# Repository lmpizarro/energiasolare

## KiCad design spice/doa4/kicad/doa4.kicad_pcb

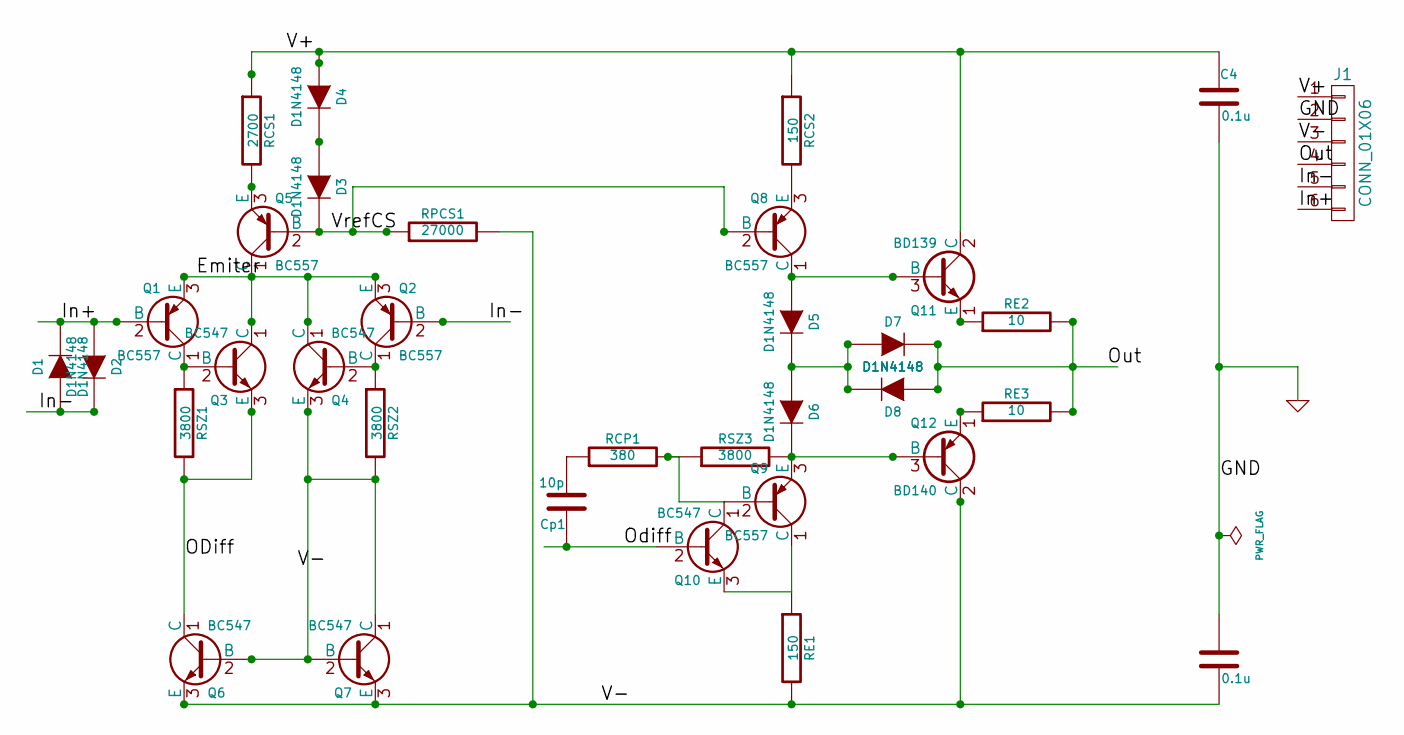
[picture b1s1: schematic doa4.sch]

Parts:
C4, C5: 0.1u; C_Rect_L4.6mm_W3.0mm_P2.50mm_MKS02_FKP02_Doa4
Cp1: 10p; C_Rect_L4.6mm_W3.0mm_P2.50mm_MKS02_FKP02_Doa4
D1: D1N4148; D_DO-41_SOD81_P2.54mm_Vertical_AnodeUp
D2, D3, D4, D5, D6, D7, D8: D1N4148; D_DO-41_SOD81_P2.54mm_Vertical_AnodeUp_Doa4
J1: CONN_01X06; j990
Q1, Q2, Q5, Q8, Q9: BC557; TO-92_Molded_Wide_BCXXX
Q3, Q4, Q6, Q7, Q10: BC547; TO-92_Molded_Wide_BCXXX
Q11: BD139; TO-126_Vertical_Doa4
Q12: BD140; TO-126_Vertical_Doa4
RCP1: 380; R_Axial_DIN0207_L6.3mm_D2.5mm_P2.54mm_Vertical_Doa4
RCS1: 2700; R_Axial_DIN0207_L6.3mm_D2.5mm_P2.54mm_Vertical_Doa4
RCS2: 150; R_Axial_DIN0207_L6.3mm_D2.5mm_P2.54mm_Vertical_Doa4
RE1: 150; R_Axial_DIN0207_L6.3mm_D2.5mm_P2.54mm_Vertical_Doa4
RE2, RE3: 10; R_Axial_DIN0207_L6.3mm_D2.5mm_P2.54mm_Vertical_Doa4
RPCS1: 27000; R_Axial_DIN0207_L6.3mm_D2.5mm_P2.54mm_Vertical_Doa4
RSZ1, RSZ2, RSZ3: 3800; R_Axial_DIN0207_L6.3mm_D2.5mm_P2.54mm_Vertical_Doa4

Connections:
/Emiter: Q1.3 (E), Q2.3 (E), Q3.1 (C), Q4.1 (C), Q5.1 (C)
/In+: D1.2 (K), D2.1 (A), J1.6, Q1.2 (B)
/In-: D1.1 (A), D2.2 (K), J1.5, Q2.2 (B)
/ODiff: Cp1.1, Q3.3 (E), Q6.1 (C), Q10.2 (B), RSZ1.2
/Out: D7.2 (K), D8.1 (A), J1.4, RE2.2, RE3.2
/V+: C4.1, D4.1 (A), J1.1, Q11.2 (C), RCS1.1, RCS2.1
/V-: C5.2, J1.3, Q6.3 (E), Q7.3 (E), Q12.2 (C), RE1.2, RPCS1.2
/VrefCS: D3.2 (K), Q5.2 (B), Q8.2 (B), RPCS1.1
GND: C4.2, C5.1, J1.2
unnamed: Cp1.2, RCP1.1
unnamed: D3.1 (A), D4.2 (K)
unnamed: D5.1 (A), Q8.1 (C), Q11.3 (B)
unnamed: D5.2 (K), D6.1 (A), D7.1 (A), D8.2 (K)
unnamed: D6.2 (K), Q9.3 (E), Q12.3 (B), RSZ3.2
unnamed: Q1.1 (C), Q3.2 (B), RSZ1.1
unnamed: Q2.1 (C), Q4.2 (B), RSZ2.1
unnamed: Q4.3 (E), Q6.2 (B), Q7.1 (C), Q7.2 (B), RSZ2.2
unnamed: Q5.3 (E), RCS1.2
unnamed: Q8.3 (E), RCS2.2
unnamed: Q9.2 (B), Q10.1 (C), RCP1.2, RSZ3.1
unnamed: Q9.1 (C), Q10.3 (E), RE1.1
unnamed: Q11.1 (E), RE2.1
unnamed: Q12.1 (E), RE3.1

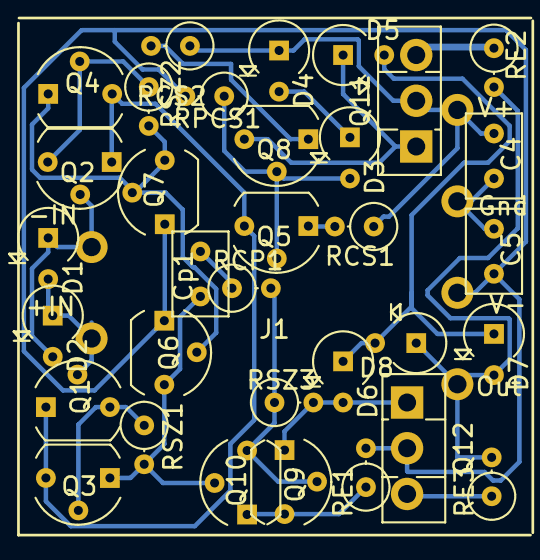
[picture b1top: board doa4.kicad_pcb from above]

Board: 2 copper layers, 34 parts (0 on the bottom side), 23 nets.

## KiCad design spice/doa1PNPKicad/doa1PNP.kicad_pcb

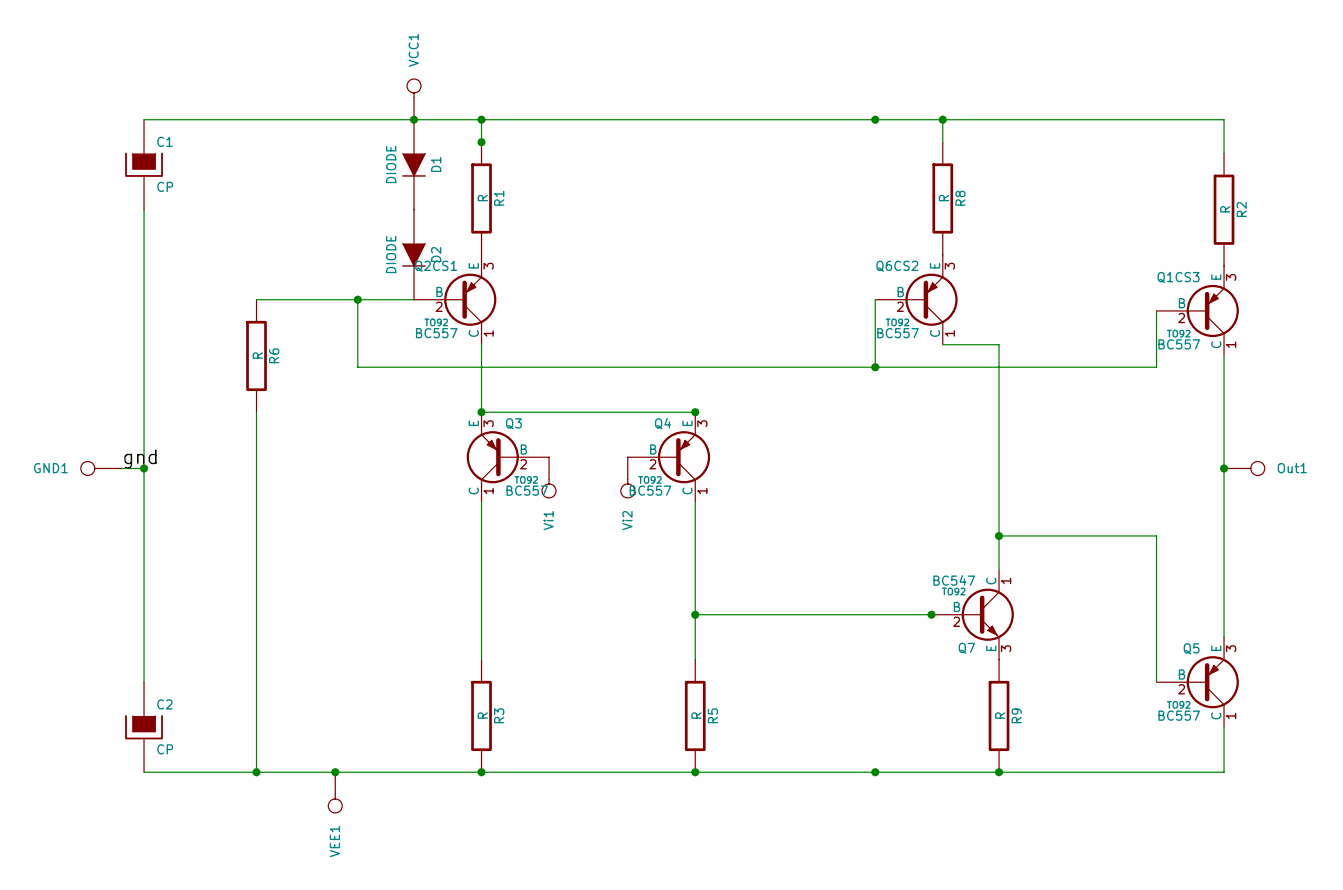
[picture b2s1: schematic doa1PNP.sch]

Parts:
C1, C2: CP
D1, D2: DIODE
GND1: CONN_1
Out1: CONN_1
Q1CS3, Q2CS1, Q3, Q4, Q5, Q6CS2: BC557; TO92
Q7: BC547; TO92
R1, R2, R3, R5, R6, R8, R9: R
VCC1: CONN_1
VEE1: CONN_1
Vi1, Vi2: CONN_1

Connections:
/gnd: C1.2, C2.1, GND1.1
unnamed: Q7.3 (E), R9.1
unnamed: Q2CS1.1 (C), Q3.3 (E), Q4.3 (E)
unnamed: Q6CS2.3 (E), R8.2
unnamed: Q5.2 (B), Q6CS2.1 (C), Q7.1 (C)
unnamed: Out1.1, Q1CS3.1 (C), Q5.3 (E)
unnamed: Q1CS3.3 (E), R2.2
unnamed: D1.2 (K), D2.1 (A)
unnamed: Q3.1 (C), R3.1
unnamed: Q4.1 (C), Q7.2 (B), R5.1
unnamed: C2.2, Q5.1 (C), R3.2, R5.2, R6.2, R9.2, VEE1.1
unnamed: Q2CS1.3 (E), R1.2
unnamed: C1.1, D1.1 (A), R1.1, R2.1, R8.1, VCC1.1
unnamed: D2.2 (K), Q1CS3.2 (B), Q2CS1.2 (B), Q6CS2.2 (B), R6.1
unnamed: Q4.2 (B), Vi2.1
unnamed: Q3.2 (B), Vi1.1

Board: 2 copper layers, 24 parts (0 on the bottom side), 16 nets, no tracks yet.

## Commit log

2017-04-07 second commit
2017-04-07 added bp solar Laudani
2017-04-07 modified one diode model
2017-04-07 module temperature dependecies
2017-04-07 module temperature dependencie Voc
2017-04-07 module temperature dependencie Imp, Vmp
2017-04-07 module temperature dependencies Iph
2017-04-10 deleted solar.py
2017-04-10 init companion.py
2017-04-10 init companion.py opencircuit
2017-04-10 init companion.py shorcircuit
2017-04-10 companion short mpp open
2017-04-10 companion added diffs
2017-04-10 modello B2
2017-04-11 bdmodulos created, class companion init
2017-04-11 mpp circuit added to companion
2017-04-11 companion cont. error pc mpp
2017-04-11 db y companion cont
2017-04-11 companion cont
2017-04-11 companion curve V-I
2017-04-11 companion fv model b2
2017-04-12 companion fv model b2 cont I0
2017-04-12 modelloB2 and companion
2017-04-12 new mpp simul companion
2017-04-12 I0 temperature dependancy
2017-04-17 modelo B3 init
2017-04-17 modelo B3 cont
2017-04-18 modello iterativo B3 init
2017-04-18 test companion added a modello iterativo b3
2017-04-18 test companion added a modello iterativo b3 cont.
2017-04-18 modello iterativo B3 cont
2017-04-19 resultados sim
2017-04-19 modelo B2 correccion Rsh
2017-04-19 modelo output resultados
2017-04-20 modello new design and model B4
2017-04-20 modello b2 calcRs
2017-04-20 simulacion modello B2
2017-04-20 simulacion modello B2 cont.
2017-04-20 simulacion modello B3 to model Base cont.
2017-04-20 more OO
2017-04-20 separacion de modulos
2017-04-21 simpleSim created
2017-04-21 modelloAmbiente creador
2017-04-21 modello ambiente actualizado
2017-04-21 temperatura to getTemperatura
2017-04-21 modeloAmbiente cont.
2017-04-21 modelloB2 correct rs = 0
2017-04-21 Datasheet csv
2017-05-17 bdModulos modificado
2017-05-17 spice electronics models added
2017-05-17 testModels added
2017-05-17 modified testModels
2017-05-18 tripler added
2017-05-18 cell model in spice init
2017-05-18 phvcell model cont.
2017-05-18 tests folder created
2017-05-18 h bridge ponte h init
2017-05-18 models tip32 & 31 added
2017-05-18 disenio 1 puente H funciona
2017-05-18 switching mosfet added
2017-05-18 modelos mosfet added
2017-05-19 reorganize spice
2017-05-19 reorganize spice cont.
2017-05-19 spice reorganize cont
2017-05-19 half wave rectifier spliter added
2017-05-19 simple doubler circuit added
2017-05-19 bufferAB low power
2017-05-19 basic potentiostat
2017-05-19 basic potentiostat cont.
2017-05-19 generic diffStage added
2017-05-19 generic diffStage added cont
2017-05-22 doa1 pnp init
2017-05-22 doa01pnp cont
2017-05-22 diff stage PNP added
2017-05-23 f resp doa1pnp
2017-05-23 doa1pnp cont
2017-05-23 project kicad doa1PNP
2017-05-24 multiple current source doa1PNP
2017-05-24 kicad out stage
2017-05-24 layout
2017-05-26 j918 begging
2017-05-30 doa4 init class ab output
2017-05-30 schema doa4 init
2017-05-30 schema doa4 cont.
2017-05-30 doa4 pcb cont
2017-06-01 pcb preDil8
2017-06-01 pcb preDil8 cont
2017-06-02 doa4.pb cont
2017-06-02 doa4 cont
2017-06-06 doa4 kicad 4.05
2017-06-06 init location input
2017-06-06 conn j990 added
2017-06-07 location init
2017-06-07 location init 2
2017-06-07 location init 3 power
2017-06-07 location init 4 q9q10
2017-06-07 location q8q5
2017-06-07 location q8q5 cont
2017-06-08 v1 complete
2017-06-08 re-locating v1
2017-06-08 re-locating v1 cont
2017-06-08 re-locating v1 cont 2
2017-06-09 RE nueva ubicacion
2017-06-15 feedback comp
2017-06-16 compensation dig pot
2017-12-19 powerSup
2018-01-18 urei op amp
2018-01-20 currentSource.cir
2018-01-21 current source
2018-02-02 pulse
